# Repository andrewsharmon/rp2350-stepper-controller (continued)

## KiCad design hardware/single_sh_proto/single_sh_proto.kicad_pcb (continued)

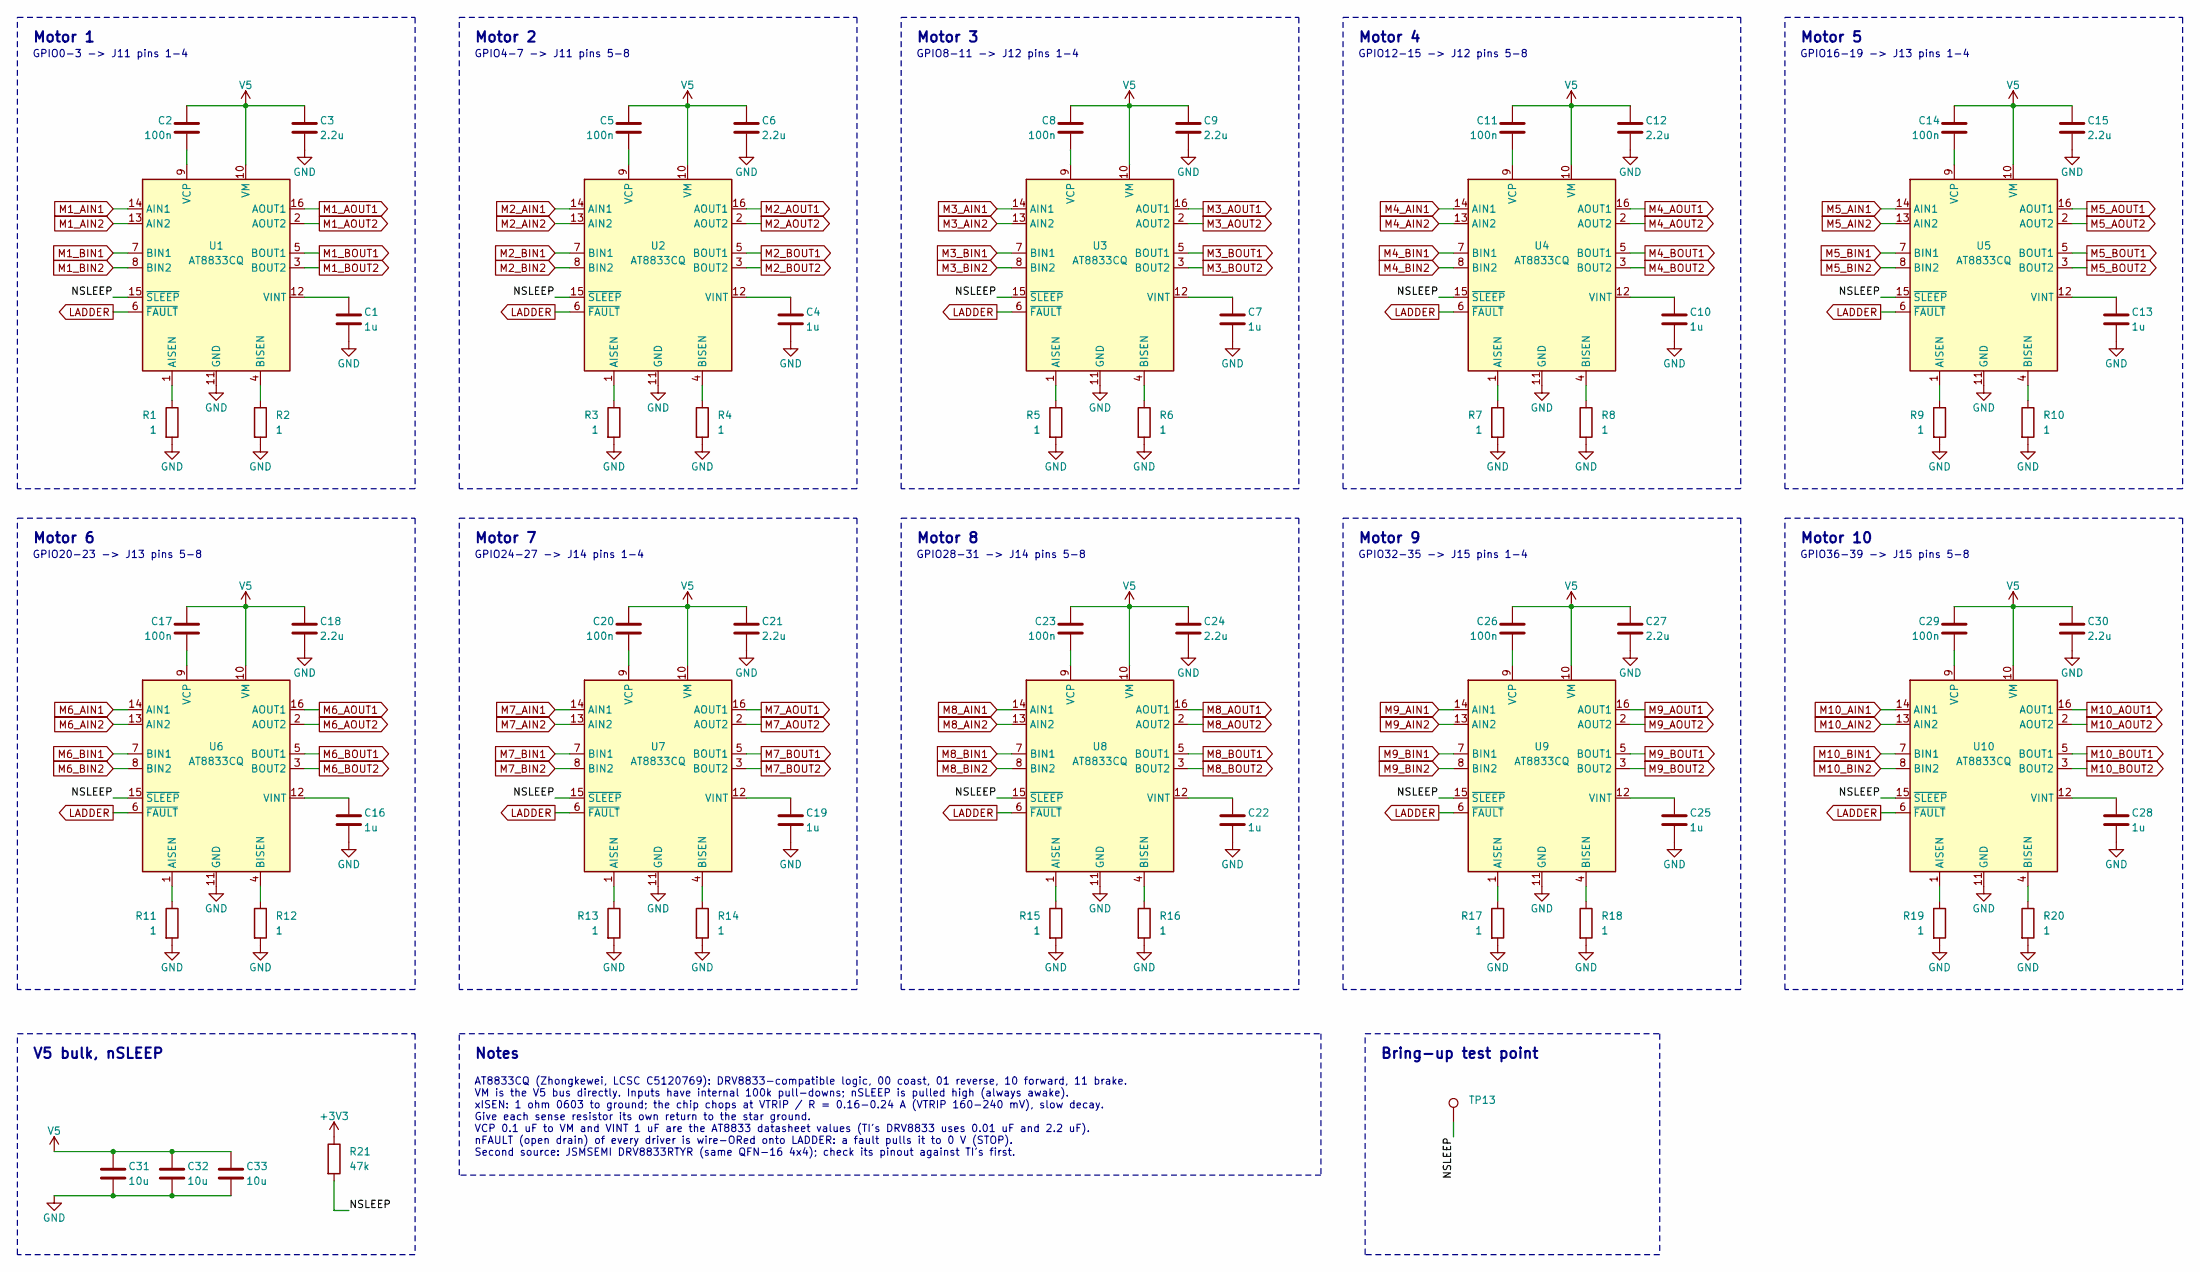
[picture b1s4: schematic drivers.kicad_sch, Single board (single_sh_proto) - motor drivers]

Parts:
C1, C4, C7, C10, C13, C16, C19, C22, C25, C28: 1u; C_0603_1608Metric; MPN CL10A105KB8NNNC; LCSC C15849
C2, C5, C8, C11, C14, C17, C20, C23, C26, C29: 100n; C_0603_1608Metric; MPN CC0603KRX7R9BB104; LCSC C14663
C3, C6, C9, C12, C15, C18, C21, C24, C27, C30: 2.2u; C_0603_1608Metric; MPN CL10A225KO8NNNC; LCSC C23630
C31, C32, C33: 10u; C_0603_1608Metric; MPN CL10A106KP8NNNC; LCSC C19702
R1, R2, R3, R4, R5, R6, R7, R8, R9, R10, R11, R12, R13, R14, R15, R16, R17, R18, R19, R20: 1; R_0603_1608Metric; MPN 0603WAF100KT5E; LCSC C22936
R21: 47k; R_0603_1608Metric; MPN 0603WAF4702T5E; LCSC C25819
TP13: NSLEEP; TestPoint_Pad_D1.0mm
U1, U2, U3, U4, U5, U6, U7, U8, U9, U10: AT8833CQ; QFN-16-1EP_4x4mm_P0.65mm_EP2.1x2.1mm; MPN AT8833CQ; LCSC C5120769

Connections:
+3V3: R21.1; also elsewhere on the board
/Motor drivers/NSLEEP: R21.2, TP13.1, U1.15 (~SLEEP), U2.15 (~SLEEP), U3.15 (~SLEEP), U4.15 (~SLEEP), U5.15 (~SLEEP), U6.15 (~SLEEP), U7.15 (~SLEEP), U8.15 (~SLEEP), U9.15 (~SLEEP), U10.15 (~SLEEP)
GND: C1.2, C3.2, C4.2, C6.2, C7.2, C9.2, C10.2, C12.2, C13.2, C15.2, C16.2, C18.2, C19.2, C21.2, C22.2, C24.2, C25.2, C27.2, C28.2, C30.2, C31.2, C32.2, C33.2, R1.2, R2.2, R3.2, R4.2, R5.2, R6.2, R7.2, R8.2, R9.2, R10.2, R11.2, R12.2, R13.2, R14.2, R15.2, R16.2, R17.2, R18.2, R19.2, R20.2, U1.11 (GND), U1.17 (GND), U2.11 (GND), U2.17 (GND), U3.11 (GND), U3.17 (GND), U4.11 (GND), U4.17 (GND), U5.11 (GND), U5.17 (GND), U6.11 (GND), U6.17 (GND), U7.11 (GND), U7.17 (GND), U8.11 (GND), U8.17 (GND), U9.11 (GND), U9.17 (GND), U10.11 (GND), U10.17 (GND); also elsewhere on the board
LADDER: U1.6 (~FAULT), U2.6 (~FAULT), U3.6 (~FAULT), U4.6 (~FAULT), U5.6 (~FAULT), U6.6 (~FAULT), U7.6 (~FAULT), U8.6 (~FAULT), U9.6 (~FAULT), U10.6 (~FAULT); also elsewhere on the board
M1_AIN1: U1.14 (AIN1); also elsewhere on the board
M1_AIN2: U1.13 (AIN2); also elsewhere on the board
M1_AOUT1: U1.16 (AOUT1); also elsewhere on the board
M1_AOUT2: U1.2 (AOUT2); also elsewhere on the board
M1_BIN1: U1.7 (BIN1); also elsewhere on the board
M1_BIN2: U1.8 (BIN2); also elsewhere on the board
M1_BOUT1: U1.5 (BOUT1); also elsewhere on the board
M1_BOUT2: U1.3 (BOUT2); also elsewhere on the board
M2_AIN1: U2.14 (AIN1); also elsewhere on the board
M2_AIN2: U2.13 (AIN2); also elsewhere on the board
M2_AOUT1: U2.16 (AOUT1); also elsewhere on the board
M2_AOUT2: U2.2 (AOUT2); also elsewhere on the board
M2_BIN1: U2.7 (BIN1); also elsewhere on the board
M2_BIN2: U2.8 (BIN2); also elsewhere on the board
M2_BOUT1: U2.5 (BOUT1); also elsewhere on the board
M2_BOUT2: U2.3 (BOUT2); also elsewhere on the board
M3_AIN1: U3.14 (AIN1); also elsewhere on the board
M3_AIN2: U3.13 (AIN2); also elsewhere on the board
M3_AOUT1: U3.16 (AOUT1); also elsewhere on the board
M3_AOUT2: U3.2 (AOUT2); also elsewhere on the board
M3_BIN1: U3.7 (BIN1); also elsewhere on the board
M3_BIN2: U3.8 (BIN2); also elsewhere on the board
M3_BOUT1: U3.5 (BOUT1); also elsewhere on the board
M3_BOUT2: U3.3 (BOUT2); also elsewhere on the board
M4_AIN1: U4.14 (AIN1); also elsewhere on the board
M4_AIN2: U4.13 (AIN2); also elsewhere on the board
M4_AOUT1: U4.16 (AOUT1); also elsewhere on the board
M4_AOUT2: U4.2 (AOUT2); also elsewhere on the board
M4_BIN1: U4.7 (BIN1); also elsewhere on the board
M4_BIN2: U4.8 (BIN2); also elsewhere on the board
M4_BOUT1: U4.5 (BOUT1); also elsewhere on the board
M4_BOUT2: U4.3 (BOUT2); also elsewhere on the board
M5_AIN1: U5.14 (AIN1); also elsewhere on the board
M5_AIN2: U5.13 (AIN2); also elsewhere on the board
M5_AOUT1: U5.16 (AOUT1); also elsewhere on the board
M5_AOUT2: U5.2 (AOUT2); also elsewhere on the board
M5_BIN1: U5.7 (BIN1); also elsewhere on the board
M5_BIN2: U5.8 (BIN2); also elsewhere on the board
M5_BOUT1: U5.5 (BOUT1); also elsewhere on the board
M5_BOUT2: U5.3 (BOUT2); also elsewhere on the board
M6_AIN1: U6.14 (AIN1); also elsewhere on the board
M6_AIN2: U6.13 (AIN2); also elsewhere on the board
M6_AOUT1: U6.16 (AOUT1); also elsewhere on the board
M6_AOUT2: U6.2 (AOUT2); also elsewhere on the board
M6_BIN1: U6.7 (BIN1); also elsewhere on the board
M6_BIN2: U6.8 (BIN2); also elsewhere on the board
M6_BOUT1: U6.5 (BOUT1); also elsewhere on the board
M6_BOUT2: U6.3 (BOUT2); also elsewhere on the board
M7_AIN1: U7.14 (AIN1); also elsewhere on the board
M7_AIN2: U7.13 (AIN2); also elsewhere on the board
M7_AOUT1: U7.16 (AOUT1); also elsewhere on the board
M7_AOUT2: U7.2 (AOUT2); also elsewhere on the board
M7_BIN1: U7.7 (BIN1); also elsewhere on the board
M7_BIN2: U7.8 (BIN2); also elsewhere on the board
M7_BOUT1: U7.5 (BOUT1); also elsewhere on the board
M7_BOUT2: U7.3 (BOUT2); also elsewhere on the board
M8_AIN1: U8.14 (AIN1); also elsewhere on the board
M8_AIN2: U8.13 (AIN2); also elsewhere on the board
M8_AOUT1: U8.16 (AOUT1); also elsewhere on the board
M8_AOUT2: U8.2 (AOUT2); also elsewhere on the board
M8_BIN1: U8.7 (BIN1); also elsewhere on the board
M8_BIN2: U8.8 (BIN2); also elsewhere on the board
M8_BOUT1: U8.5 (BOUT1); also elsewhere on the board
M8_BOUT2: U8.3 (BOUT2); also elsewhere on the board
M9_AIN1: U9.14 (AIN1); also elsewhere on the board
M9_AIN2: U9.13 (AIN2); also elsewhere on the board
M9_AOUT1: U9.16 (AOUT1); also elsewhere on the board
M9_AOUT2: U9.2 (AOUT2); also elsewhere on the board
M9_BIN1: U9.7 (BIN1); also elsewhere on the board
M9_BIN2: U9.8 (BIN2); also elsewhere on the board
M9_BOUT1: U9.5 (BOUT1); also elsewhere on the board
M9_BOUT2: U9.3 (BOUT2); also elsewhere on the board
M10_AIN1: U10.14 (AIN1); also elsewhere on the board
M10_AIN2: U10.13 (AIN2); also elsewhere on the board
M10_AOUT1: U10.16 (AOUT1); also elsewhere on the board
M10_AOUT2: U10.2 (AOUT2); also elsewhere on the board
M10_BIN1: U10.7 (BIN1); also elsewhere on the board
M10_BIN2: U10.8 (BIN2); also elsewhere on the board
M10_BOUT1: U10.5 (BOUT1); also elsewhere on the board
M10_BOUT2: U10.3 (BOUT2); also elsewhere on the board
unnamed: R1.1, U1.1 (AISEN)
unnamed: R2.1, U1.4 (BISEN)
unnamed: C2.1, U1.9 (VCP)
unnamed: C1.1, U1.12 (VINT)
unnamed: R3.1, U2.1 (AISEN)
unnamed: R4.1, U2.4 (BISEN)
unnamed: C5.1, U2.9 (VCP)
unnamed: C4.1, U2.12 (VINT)
unnamed: R5.1, U3.1 (AISEN)
unnamed: R6.1, U3.4 (BISEN)
unnamed: C8.1, U3.9 (VCP)
unnamed: C7.1, U3.12 (VINT)
unnamed: R7.1, U4.1 (AISEN)
unnamed: R8.1, U4.4 (BISEN)
unnamed: C11.1, U4.9 (VCP)
unnamed: C10.1, U4.12 (VINT)
unnamed: R9.1, U5.1 (AISEN)
unnamed: R10.1, U5.4 (BISEN)
unnamed: C14.1, U5.9 (VCP)
unnamed: C13.1, U5.12 (VINT)
unnamed: R11.1, U6.1 (AISEN)
unnamed: R12.1, U6.4 (BISEN)
unnamed: C17.1, U6.9 (VCP)
unnamed: C16.1, U6.12 (VINT)
unnamed: R13.1, U7.1 (AISEN)
unnamed: R14.1, U7.4 (BISEN)
unnamed: C20.1, U7.9 (VCP)
unnamed: C19.1, U7.12 (VINT)
unnamed: R15.1, U8.1 (AISEN)
unnamed: R16.1, U8.4 (BISEN)
unnamed: C23.1, U8.9 (VCP)
unnamed: C22.1, U8.12 (VINT)
unnamed: R17.1, U9.1 (AISEN)
unnamed: R18.1, U9.4 (BISEN)
unnamed: C26.1, U9.9 (VCP)
unnamed: C25.1, U9.12 (VINT)
unnamed: R19.1, U10.1 (AISEN)
unnamed: R20.1, U10.4 (BISEN)
unnamed: C29.1, U10.9 (VCP)
unnamed: C28.1, U10.12 (VINT)
V5: C2.2, C3.1, C5.2, C6.1, C8.2, C9.1, C11.2, C12.1, C14.2, C15.1, C17.2, C18.1, C20.2, C21.1, C23.2, C24.1, C26.2, C27.1, C29.2, C30.1, C31.1, C32.1, C33.1, U1.10 (VM), U2.10 (VM), U3.10 (VM), U4.10 (VM), U5.10 (VM), U6.10 (VM), U7.10 (VM), U8.10 (VM), U9.10 (VM), U10.10 (VM); also elsewhere on the board

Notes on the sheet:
Motor 1
GPIO0-3 -> J11 pins 1-4
Motor 2
GPIO4-7 -> J11 pins 5-8
Motor 3
GPIO8-11 -> J12 pins 1-4
Motor 4
GPIO12-15 -> J12 pins 5-8
Motor 5
GPIO16-19 -> J13 pins 1-4
Motor 6
GPIO20-23 -> J13 pins 5-8
Motor 7
GPIO24-27 -> J14 pins 1-4
Motor 8
GPIO28-31 -> J14 pins 5-8
Motor 9
GPIO32-35 -> J15 pins 1-4
Motor 10
GPIO36-39 -> J15 pins 5-8
V5 bulk, nSLEEP
Notes
AT8833CQ (Zhongkewei, LCSC C5120769): DRV8833-compatible logic, 00 coast, 01 reverse, 10 forward, 11 brake. VM is the V5 bus directly. Inputs have internal 100k pull-downs; nSLEEP is pulled high (always awake). xISEN: 1 ohm 0603 to ground; the chip chops at VTRIP / R = 0.16-0.24 A (VTRIP 160-240 mV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
Bring-up test point

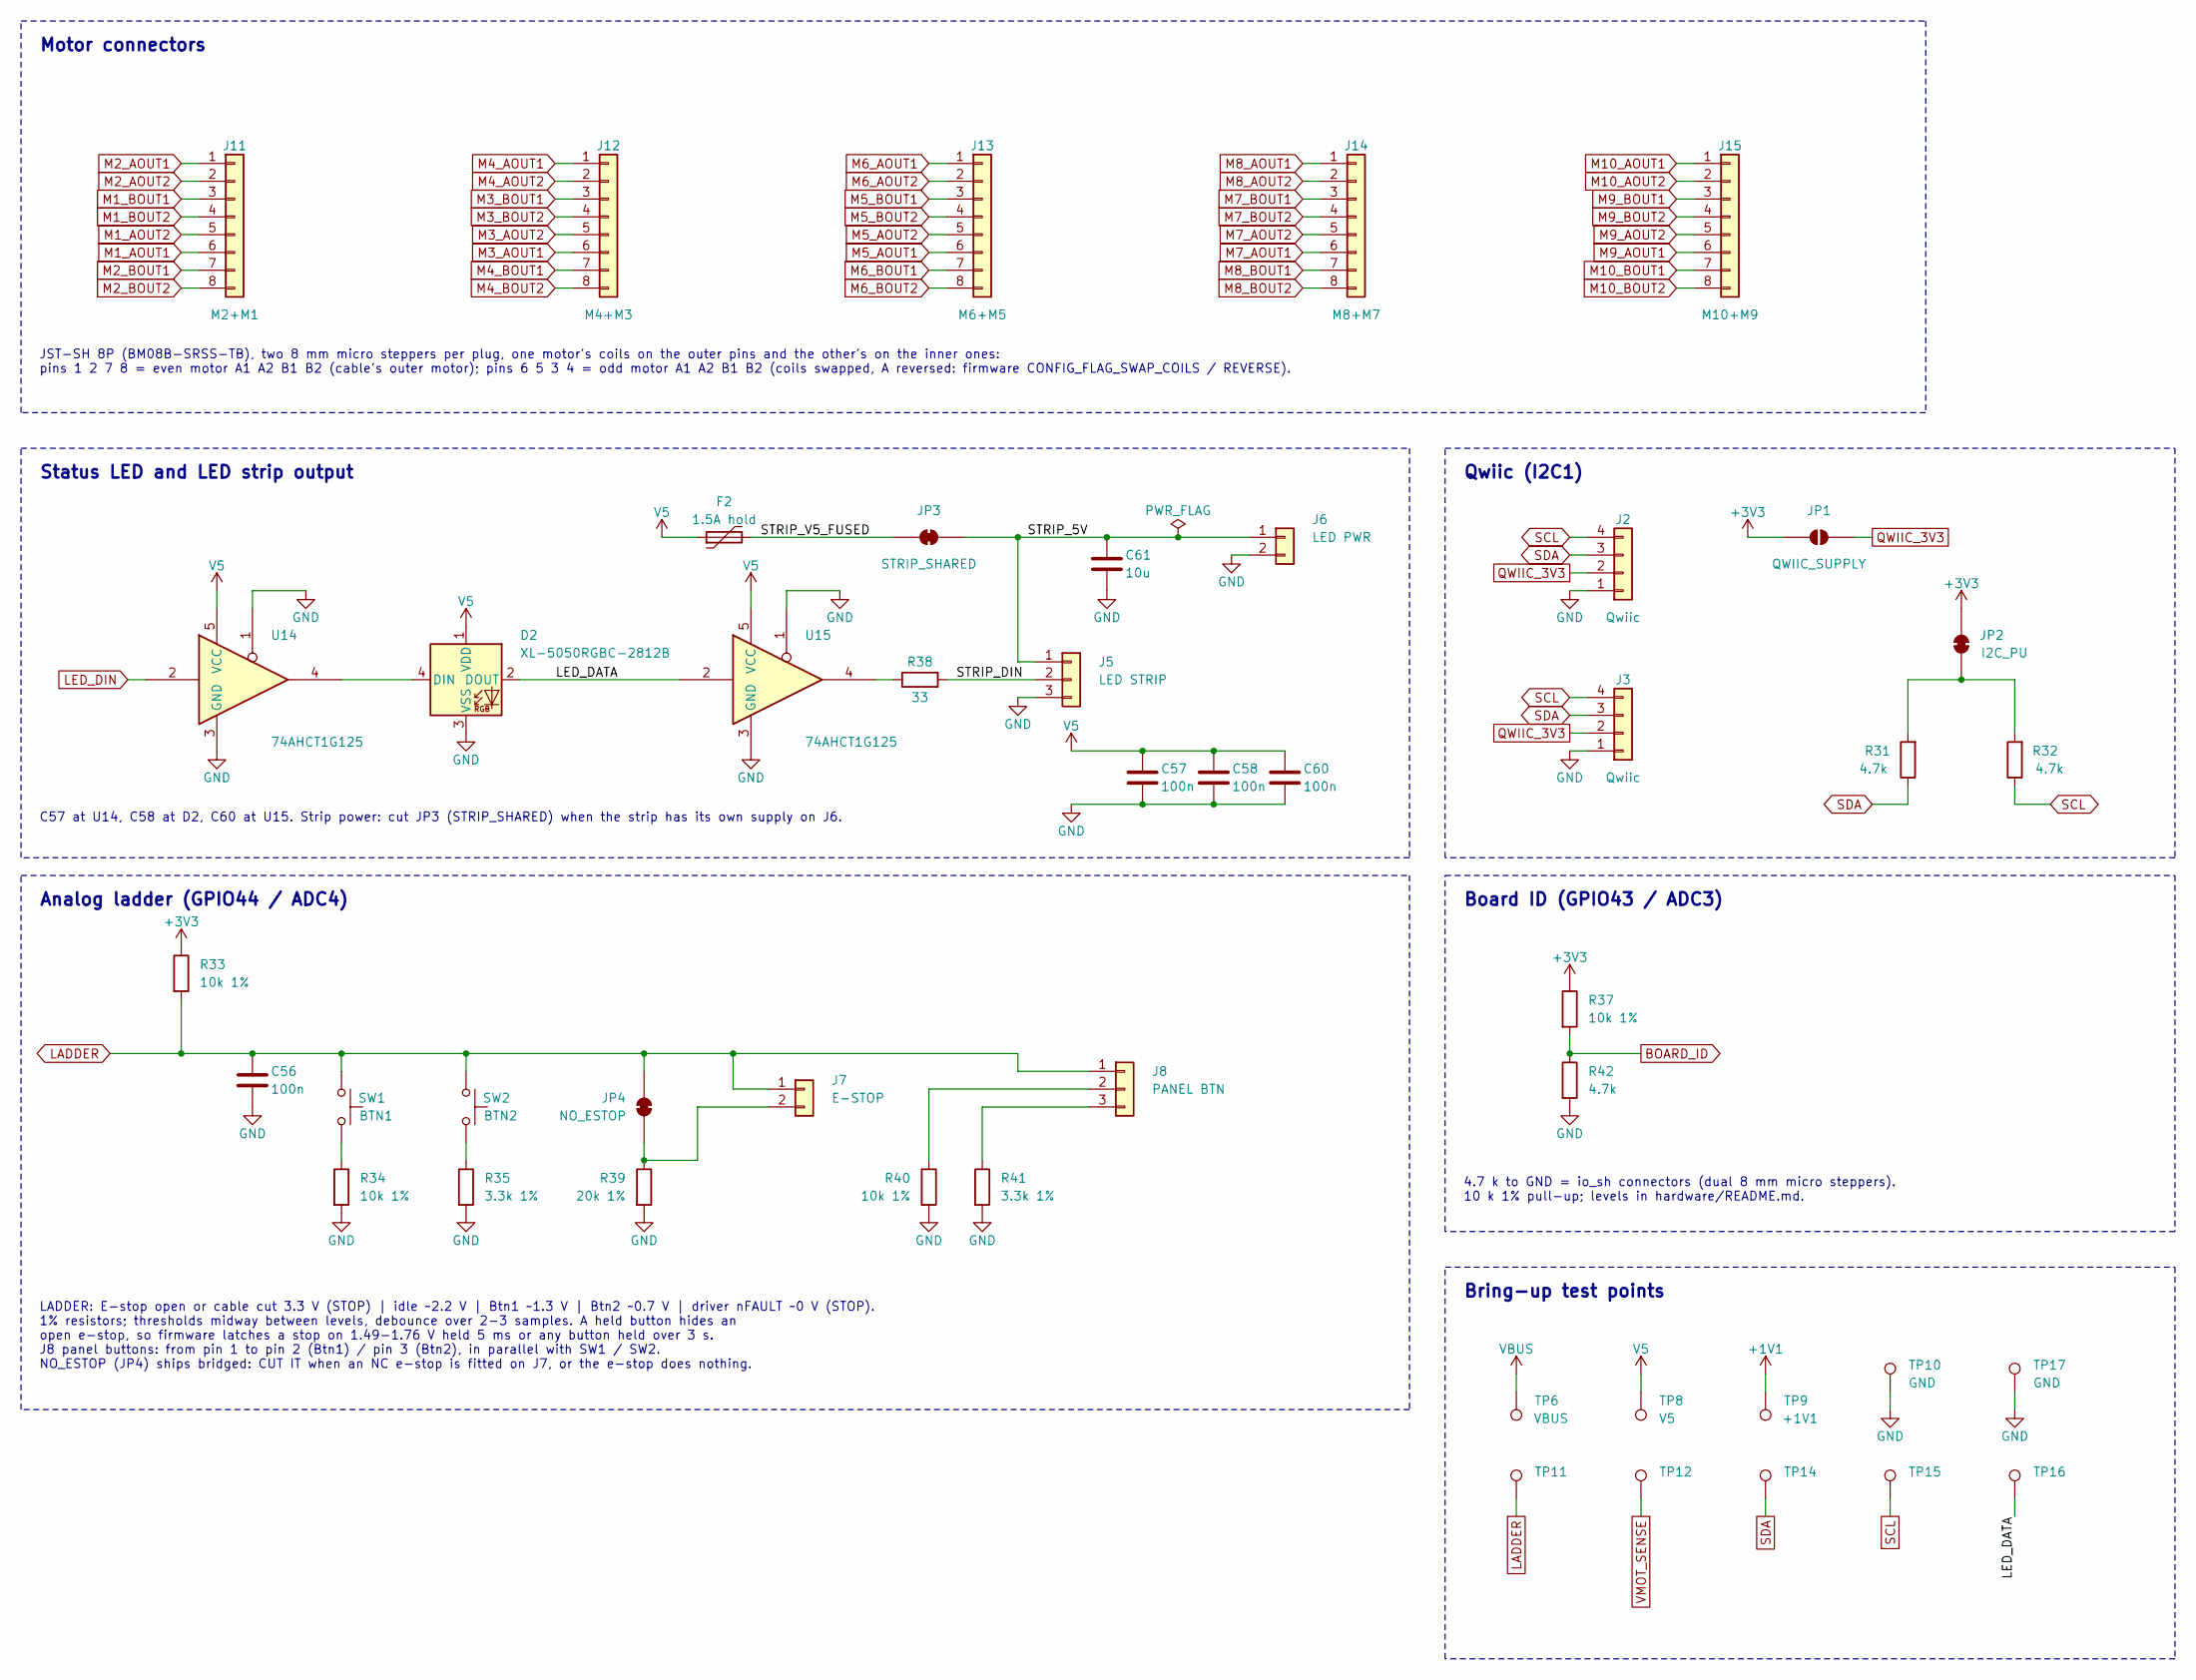
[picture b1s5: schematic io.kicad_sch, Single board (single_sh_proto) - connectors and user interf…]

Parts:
C56, C57, C58, C60: 100n; C_0603_1608Metric; MPN CC0603KRX7R9BB104; LCSC C14663
C61: 10u; C_0603_1608Metric; MPN CL10A106KP8NNNC; LCSC C19702
D2: XL-5050RGBC-2812B; LED_WS2812B_PLCC4_5.0x5.0mm_P3.2mm; MPN XL-5050RGBC-2812B; LCSC C2843785
F2: 1.5A hold; Fuse_1812_4532Metric; MPN SMD1812P150TF/8; LCSC C209721
J2, J3: Qwiic; JST_SH_BM04B-SRSS-TB_1x04-1MP_P1.00mm_Vertical; MPN BM04B-SRSS-TB; LCSC C160390
J5: LED STRIP; JST_XH_B3B-XH-A_1x03_P2.50mm_Vertical; MPN B3B-XH-A; LCSC C144394
J6: LED PWR; JST_PH_B2B-PH-K_1x02_P2.00mm_Vertical; MPN B2B-PH-K-S; LCSC C131337
J7: E-STOP; JST_PH_B2B-PH-K_1x02_P2.00mm_Vertical; MPN B2B-PH-K-S; LCSC C131337
J8: PANEL BTN; JST_PH_B3B-PH-K_1x03_P2.00mm_Vertical; MPN B3B-PH-K-S; LCSC C131339
J11: M2+M1; JST_SH_BM08B-SRSS-TB_1x08-1MP_P1.00mm_Vertical; MPN BM08B-SRSS-TB; LCSC C160394
J12: M4+M3; JST_SH_BM08B-SRSS-TB_1x08-1MP_P1.00mm_Vertical; MPN BM08B-SRSS-TB; LCSC C160394
J13: M6+M5; JST_SH_BM08B-SRSS-TB_1x08-1MP_P1.00mm_Vertical; MPN BM08B-SRSS-TB; LCSC C160394
J14: M8+M7; JST_SH_BM08B-SRSS-TB_1x08-1MP_P1.00mm_Vertical; MPN BM08B-SRSS-TB; LCSC C160394
J15: M10+M9; JST_SH_BM08B-SRSS-TB_1x08-1MP_P1.00mm_Vertical; MPN BM08B-SRSS-TB; LCSC C160394
JP1: QWIIC_SUPPLY; SolderJumper-2_P1.3mm_Open_RoundedPad1.0x1.5mm
JP2: I2C_PU; SolderJumper-2_P1.3mm_Bridged_RoundedPad1.0x1.5mm
JP3: STRIP_SHARED; SolderJumper-2_P1.3mm_Bridged_RoundedPad1.0x1.5mm
JP4: NO_ESTOP; SolderJumper-2_P1.3mm_Bridged_RoundedPad1.0x1.5mm
R31, R32, R42: 4.7k; R_0603_1608Metric; MPN 0603WAF4701T5E; LCSC C23162
R33, R34, R37, R40: 10k 1%; R_0603_1608Metric; MPN 0603WAF1002T5E; LCSC C25804
R35, R41: 3.3k 1%; R_0603_1608Metric; MPN 0603WAF3301T5E; LCSC C22978
R38: 33; R_0603_1608Metric; MPN 0603WAF330JT5E; LCSC C23140
R39: 20k 1%; R_0603_1608Metric; MPN 0603WAF2002T5E; LCSC C4184
SW1: BTN1; SW_SPST_TS-1088-xR020; MPN TS-1088-AR02016; LCSC C720477
SW2: BTN2; SW_SPST_TS-1088-xR020; MPN TS-1088-AR02016; LCSC C720477
TP6: VBUS; TestPoint_Pad_D1.0mm
TP8: V5; TestPoint_Pad_D1.0mm
TP9: +1V1; TestPoint_Pad_D1.0mm
TP10, TP17: GND; TestPoint_Pad_D1.0mm
TP11: LADDER; TestPoint_Pad_D1.0mm
TP12: VMOT_SENSE; TestPoint_Pad_D1.0mm
TP14: SDA; TestPoint_Pad_D1.0mm
TP15: SCL; TestPoint_Pad_D1.0mm
TP16: LED_DATA; TestPoint_Pad_D1.0mm
U14, U15: 74AHCT1G125; SOT-23-5; MPN SN74AHCT1G125DBVR; LCSC C7484

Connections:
+1V1: TP9.1; also elsewhere on the board
+3V3: JP1.1 (A), JP2.2 (B), R33.1, R37.1; also elsewhere on the board
/Connectors and UI/LED_DATA: D2.2 (DOUT), TP16.1, U15.2
/Connectors and UI/STRIP_5V: C61.1, J5.1, J6.1, JP3.2 (B)
/Connectors and UI/STRIP_DIN: J5.2, R38.2
/Connectors and UI/STRIP_V5_FUSED: F2.2, JP3.1 (A)
BOARD_ID: R37.2, R42.1; also elsewhere on the board
GND: C56.2, C57.2, C58.2, C60.2, C61.2, D2.3 (VSS), J2.1, J3.1, J5.3, J6.2, R34.2, R35.2, R39.2, R40.2, R41.2, R42.2, TP10.1, TP17.1, U14.1, U14.3 (GND), U15.1, U15.3 (GND); also elsewhere on the board
LADDER: C56.1, J7.1, J8.1, JP4.1 (A), R33.2, SW1.1, SW2.1, TP11.1; also elsewhere on the board
LED_DIN: U14.2; also elsewhere on the board
M1_AOUT1: J11.6; also elsewhere on the board
M1_AOUT2: J11.5; also elsewhere on the board
M1_BOUT1: J11.3; also elsewhere on the board
M1_BOUT2: J11.4; also elsewhere on the board
M2_AOUT1: J11.1; also elsewhere on the board
M2_AOUT2: J11.2; also elsewhere on the board
M2_BOUT1: J11.7; also elsewhere on the board
M2_BOUT2: J11.8; also elsewhere on the board
M3_AOUT1: J12.6; also elsewhere on the board
M3_AOUT2: J12.5; also elsewhere on the board
M3_BOUT1: J12.3; also elsewhere on the board
M3_BOUT2: J12.4; also elsewhere on the board
M4_AOUT1: J12.1; also elsewhere on the board
M4_AOUT2: J12.2; also elsewhere on the board
M4_BOUT1: J12.7; also elsewhere on the board
M4_BOUT2: J12.8; also elsewhere on the board
M5_AOUT1: J13.6; also elsewhere on the board
M5_AOUT2: J13.5; also elsewhere on the board
M5_BOUT1: J13.3; also elsewhere on the board
M5_BOUT2: J13.4; also elsewhere on the board
M6_AOUT1: J13.1; also elsewhere on the board
M6_AOUT2: J13.2; also elsewhere on the board
M6_BOUT1: J13.7; also elsewhere on the board
M6_BOUT2: J13.8; also elsewhere on the board
M7_AOUT1: J14.6; also elsewhere on the board
M7_AOUT2: J14.5; also elsewhere on the board
M7_BOUT1: J14.3; also elsewhere on the board
M7_BOUT2: J14.4; also elsewhere on the board
M8_AOUT1: J14.1; also elsewhere on the board
M8_AOUT2: J14.2; also elsewhere on the board
M8_BOUT1: J14.7; also elsewhere on the board
M8_BOUT2: J14.8; also elsewhere on the board
M9_AOUT1: J15.6; also elsewhere on the board
M9_AOUT2: J15.5; also elsewhere on the board
M9_BOUT1: J15.3; also elsewhere on the board
M9_BOUT2: J15.4; also elsewhere on the board
M10_AOUT1: J15.1; also elsewhere on the board
M10_AOUT2: J15.2; also elsewhere on the board
M10_BOUT1: J15.7; also elsewhere on the board
M10_BOUT2: J15.8; also elsewhere on the board
unnamed: D2.4 (DIN), U14.4
unnamed: J7.2, JP4.2 (B), R39.1
unnamed: J8.2, R40.1
unnamed: J8.3, R41.1
unnamed: JP2.1 (A), R31.2, R32.2
unnamed: R34.1, SW1.2
unnamed: R35.1, SW2.2
unnamed: R38.1, U15.4
QWIIC_3V3: J2.2, J3.2, JP1.2 (B)
SCL: J2.4, J3.4, R32.1, TP15.1; also elsewhere on the board
SDA: J2.3, J3.3, R31.1, TP14.1; also elsewhere on the board
V5: C57.1, C58.1, C60.1, D2.1 (VDD), F2.1, TP8.1, U14.5 (VCC), U15.5 (VCC); also elsewhere on the board
VBUS: TP6.1; also elsewhere on the board
VMOT_SENSE: TP12.1; also elsewhere on the board

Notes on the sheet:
Motor connectors
JST-SH 8P (BM08B-SRSS-TB), two 8 mm micro steppers per plug, one motor's coils on the outer pins and the other's on the inner ones: pins 1 2 7 8 = even motor A1 A2 B1 B2 (cable's outer motor); pins 6 5 3 4 = odd motor A1 A2 B1 B2 (coils swapped, A reversed: firmware CONFIG_FLAG_SWAP_COILS / REVERSE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
Status LED and LED strip output
C57 at U14, C58 at D2, C60 at U15. Strip power: cut JP3 (STRIP_SHARED) when the strip has its own supply on J6.
Qwiic (I2C1)
Analog ladder (GPIO44 / ADC4)
LADDER: E-stop open or cable cut 3.3 V (STOP) | idle ~2.2 V | Btn1 ~1.3 V | Btn2 ~0.7 V | driver nFAULT ~0 V (STOP). 1% resistors; thresholds midway between levels, debounce over 2-3 samples. A held button hides an open e-stop, so firmware latches a stop on 1.49-1.76 V held 5 ms or any button held 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
Board ID (GPIO43 / ADC3)
4.7 k to GND = io_sh connectors (dual 8 mm micro steppers). 10 k 1% pull-up; levels in hardware/README.md.
Bring-up test points

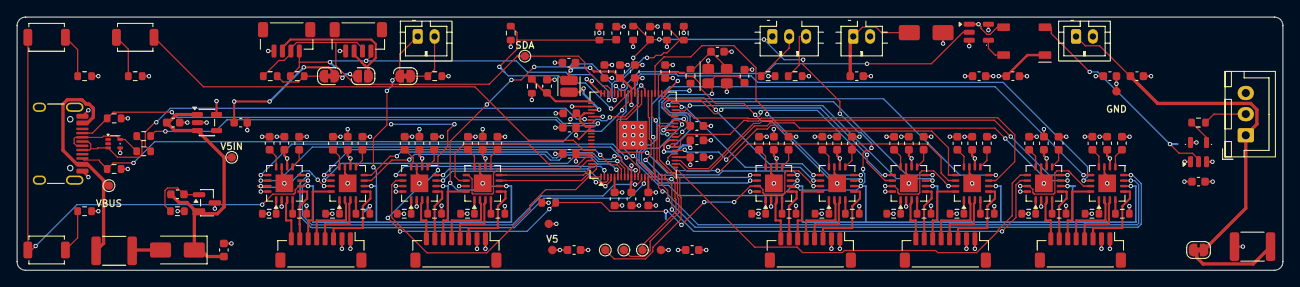
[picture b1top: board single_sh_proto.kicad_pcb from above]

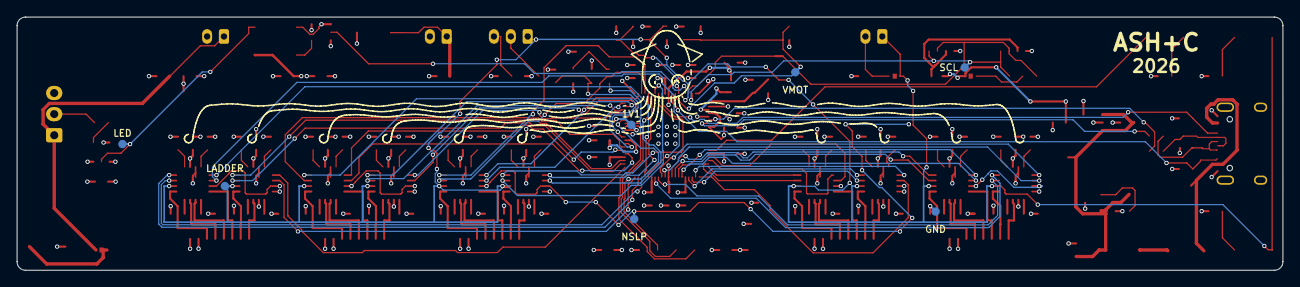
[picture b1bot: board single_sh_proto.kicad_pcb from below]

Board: 4 copper layers, 150.0 x 30.0 mm, 163 parts (7 on the bottom side), 165 nets.

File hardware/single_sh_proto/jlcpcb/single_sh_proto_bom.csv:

Comment,Designator,Footprint,LCSC Part #
1u,"C1,C4,C7,C10,C13,C16,C19,C22,C25,C28,C53,C55,C59",C_0603_1608Metric,C15849
100n,"C2,C5,C8,C11,C14,C17,C20,C23,C26,C29,C34,C35,C36,C37,C38,C39,C40,C41,C42,C43,C45,C46,C47,C54,C56,C57,C58,C60",C_0603_1608Metric,C14663
2.2u,"C3,C6,C9,C12,C15,C18,C21,C24,C27,C30",C_0603_1608Metric,C23630
10u,"C31,C32,C33,C52,C61",C_0603_1608Metric,C19702
4.7u,"C44,C48,C49",C_0603_1608Metric,C19666
15p,"C50,C51",C_0603_1608Metric,C1644
SS54,"D1,D3",D_SMA,C22452
XL-5050RGBC-2812B,D2,LED_WS2812B_PLCC4_5.0x5.0mm_P3.2mm,C2843785
1.5A hold,"F1,F2",Fuse_1812_4532Metric,C209721
USB-C,J1,USB_C_Receptacle_HRO_TYPE-C-31-M-12,C165948
Qwiic,"J2,J3",JST_SH_BM04B-SRSS-TB_1x04-1MP_P1.00mm_Vertical,C160390
5V IN / LED PWR / E-STOP,"J4,J6,J7",JST_PH_B2B-PH-K_1x02_P2.00mm_Vertical,C131337
LED STRIP,J5,JST_XH_B3B-XH-A_1x03_P2.50mm_Vertical,C144394
PANEL BTN,J8,JST_PH_B3B-PH-K_1x03_P2.00mm_Vertical,C131339
M2+M1 / M4+M3 / M6+M5 / M8+M7 / M10+M9,"J11,J12,J13,J14,J15",JST_SH_BM08B-SRSS-TB_1x08-1MP_P1.00mm_Vertical,C160394
3.3u,L1,L_Cenker_CKCS201610,C411344
AO3401A,Q1,SOT-23,C15127
1,"R1,R2,R3,R4,R5,R6,R7,R8,R9,R10,R11,R12,R13,R14,R15,R16,R17,R18,R19,R20",R_0603_1608Metric,C22936
47k,R21,R_0603_1608Metric,C25819
39k 1%,R22,R_0603_1608Metric,C23153
10k 1%,"R23,R33,R34,R37,R40",R_0603_1608Metric,C25804
33,"R24,R38",R_0603_1608Metric,C23140
1k,"R25,R36",R_0603_1608Metric,C21190
22,"R26,R27",R_0603_1608Metric,C23345
5.1k,"R28,R29",R_0603_1608Metric,C23186
100k,R30,R_0603_1608Metric,C25803
4.7k,"R31,R32,R42",R_0603_1608Metric,C23162
3.3k 1%,"R35,R41",R_0603_1608Metric,C22978
20k 1%,R39,R_0603_1608Metric,C4184
BTN1 / BTN2 / BOOTSEL,"SW1,SW2,SW3",SW_SPST_TS-1088-xR020,C720477
AT8833CQ,"U1,U2,U3,U4,U5,U6,U7,U8,U9,U10",QFN-16-1EP_4x4mm_P0.65mm_EP2.1x2.1mm,C5120769
RP2354B,U11,QFN-80-1EP_10x10mm_P0.4mm_EP3.4x3.4mm,C39843328
TPD2E2U06,U12,SOT-553,C1972959
ME6211C33M5G,U13,SOT-23-5,C82942
74AHCT1G125,"U14,U15",SOT-23-5,C7484
12MHz,Y1,Crystal_SMD_3225-4Pin_3.2x2.5mm,C20625731
